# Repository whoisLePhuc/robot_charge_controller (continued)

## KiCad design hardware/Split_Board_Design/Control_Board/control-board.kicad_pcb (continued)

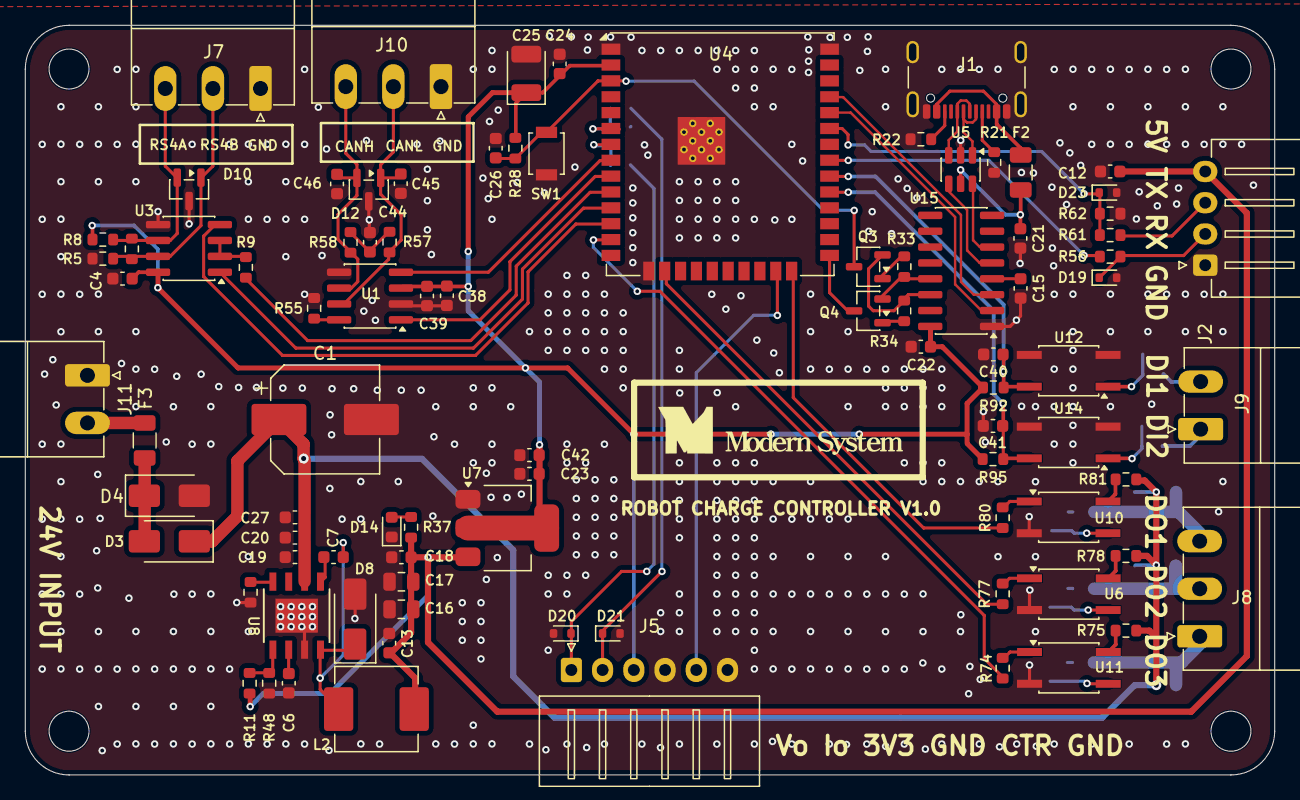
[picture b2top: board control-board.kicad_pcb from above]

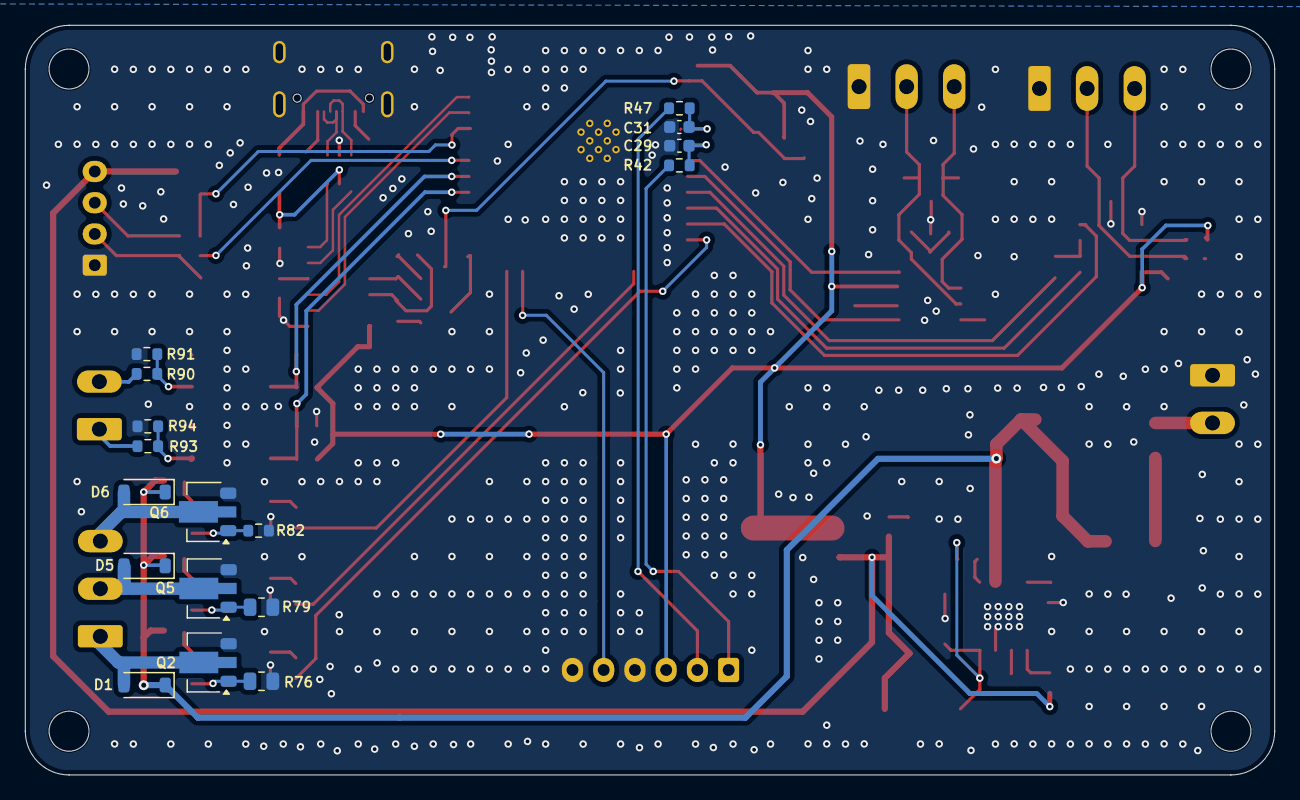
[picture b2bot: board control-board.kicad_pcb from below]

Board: 2 copper layers, 100.0 x 60.0 mm, 111 parts (17 on the bottom side), 71 nets.
